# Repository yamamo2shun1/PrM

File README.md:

PrM
===

Modularized Analog mixer Controlled by Open Sound Control

License
---
<br /><span xmlns:dct="http://purl.org/dc/terms/" property="dct:title">PrM</span> is licensed under a <a rel="license" href="http://creativecommons.org/licenses/by-sa/4.0/">Creative Commons Attribution-ShareAlike 4.0 International License</a>.<br />Based on a work at <a xmlns:dct="http://purl.org/dc/terms/" href="https://github.com/tkrworks/PrM" rel="dct:source">https://github.com/tkrworks/PrM</a>.

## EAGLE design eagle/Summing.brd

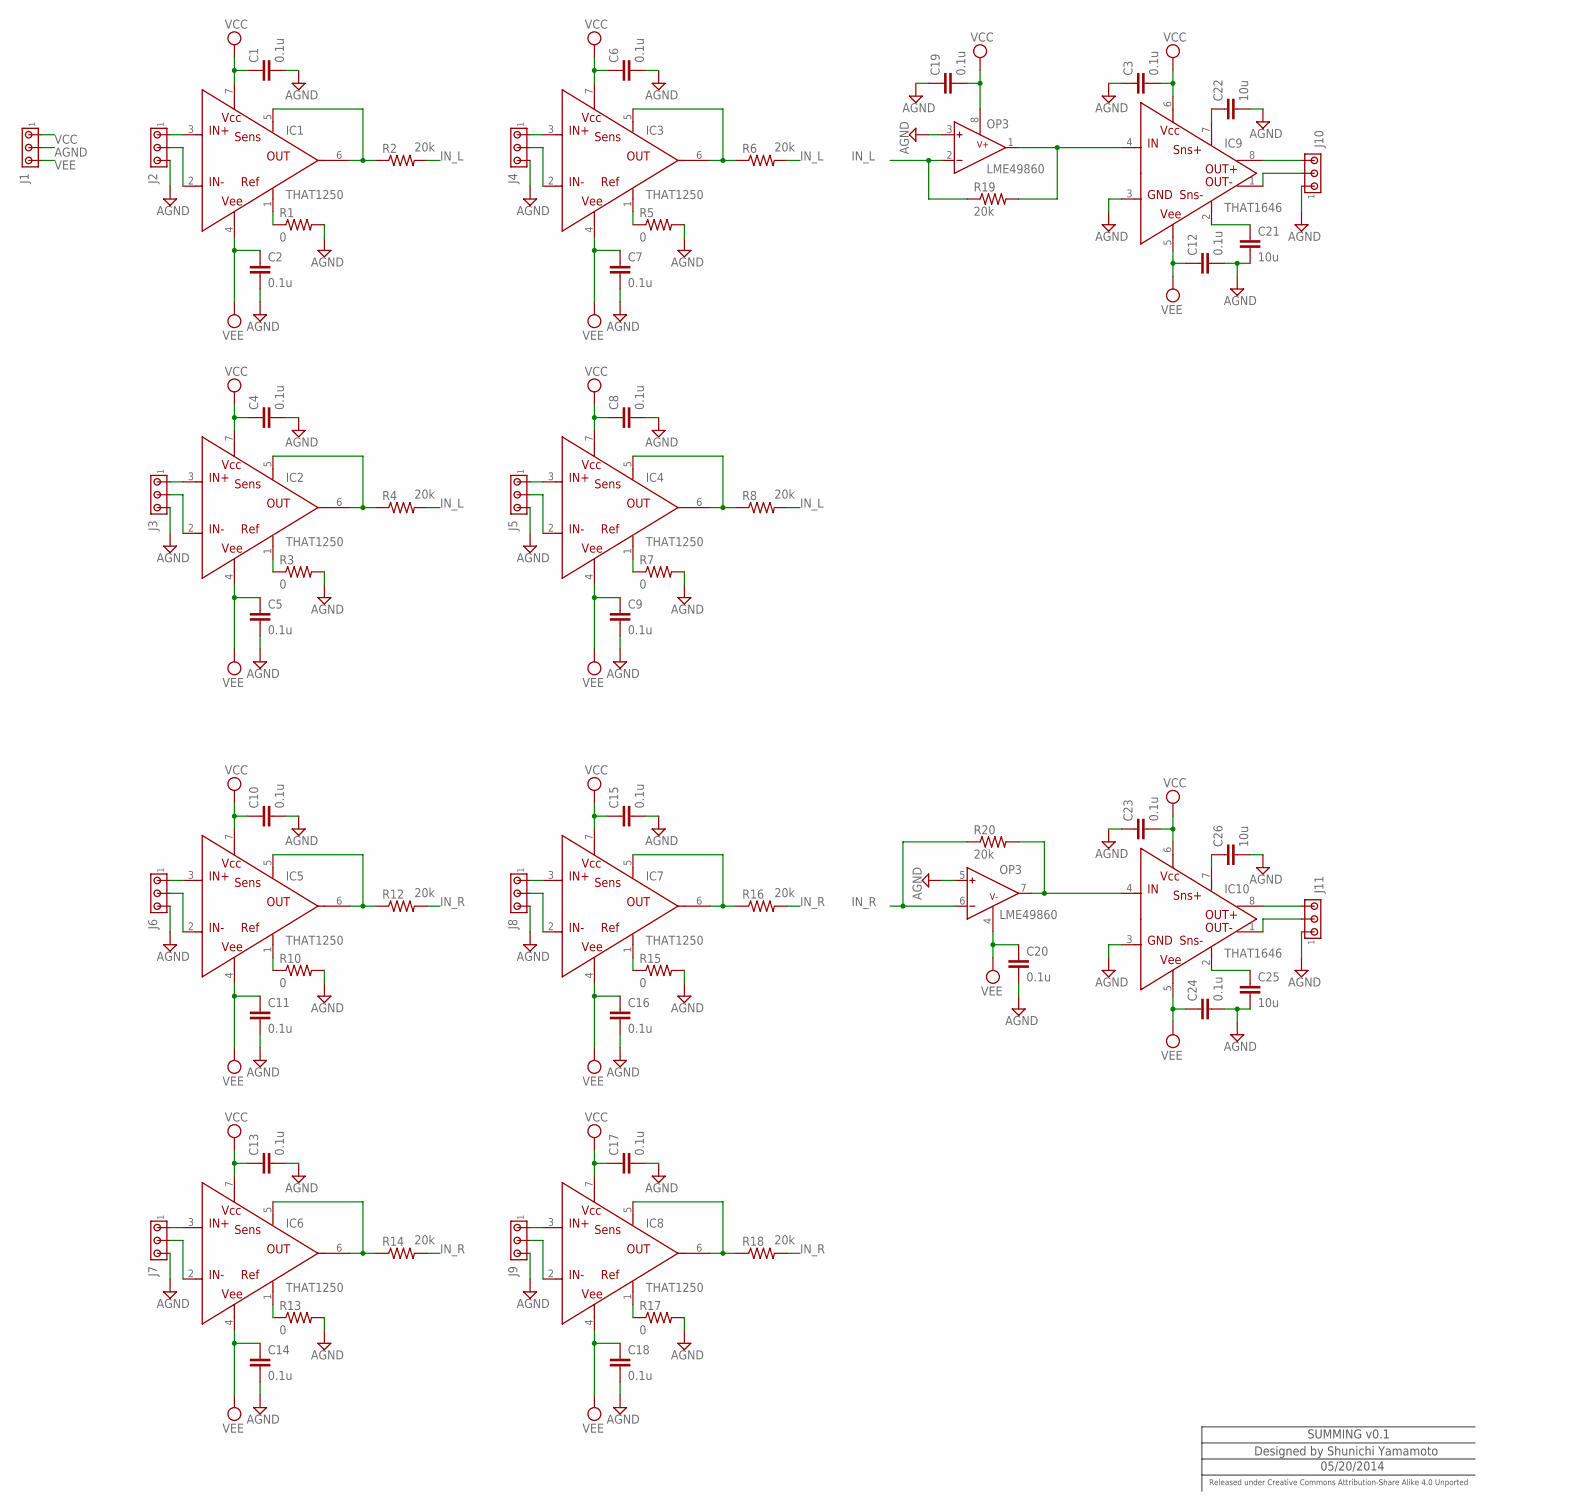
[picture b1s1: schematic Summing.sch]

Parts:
C1, C2, C3, C4, C5, C6, C7, C8, C9, C10, C11, C12, C13, C14, C15, C16, C17, C18, C19, C20, C23, C24: 0.1u; C2012
C21, C22, C25, C26: 10u; C2012
IC1, IC2, IC3, IC4, IC5, IC6, IC7, IC8: THAT1250; SOIC8@1
IC9, IC10: THAT1646; SOIC8
J1: MTA03-156; 1X3MTA
J2, J3, J4, J5, J6, J7, J8, J9, J10, J11: MTA03-100; 10X03MTA
OP3: LME49860; SOIC8@2
R1, R3, R5, R7, R10, R13, R15, R17: 0; 0805
R2, R4, R6, R8, R12, R14, R16, R18, R19, R20: 20k; 0805

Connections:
AGND: C1.2, C2.2, C3.1, C4.2, C5.2, C6.2, C7.2, C8.2, C9.2, C10.2, C11.2, C12.2, C13.2, C14.2, C15.2, C16.2, C17.2, C18.2, C19.1, C20.2, C21.2, C22.2, C23.1, C24.2, C25.2, C26.2, IC9.3 (GND), IC10.3 (GND), J1.2, J2.3, J3.3, J4.3, J5.3, J6.3, J7.3, J8.3, J9.3, J10.1, J11.1, OP3.3 (INA+), OP3.5 (INB+), R1.2, R3.2, R5.2, R7.2, R10.2, R13.2, R15.2, R17.2
IN_L: OP3.2 (INA-), R2.2, R4.2, R6.2, R8.2, R19.1
IN_R: OP3.6 (INB-), R12.2, R14.2, R16.2, R18.2, R20.1
MGAIN_L2: IC9.4 (IN), OP3.1 (OUTA), R19.2
MGAIN_R: IC10.4 (IN), OP3.7 (OUTB), R20.2
unnamed: IC1.1 (REF), R1.1
unnamed: IC2.1 (REF), R3.1
unnamed: IC1.3 (IN+), J2.1
unnamed: IC1.2 (IN-), J2.2
unnamed: IC2.3 (IN+), J3.1
unnamed: IC2.2 (IN-), J3.2
unnamed: IC3.1 (REF), R5.1
unnamed: IC3.3 (IN+), J4.1
unnamed: IC3.2 (IN-), J4.2
unnamed: IC4.1 (REF), R7.1
unnamed: IC4.3 (IN+), J5.1
unnamed: IC4.2 (IN-), J5.2
unnamed: IC5.1 (REF), R10.1
unnamed: IC5.3 (IN+), J6.1
unnamed: IC5.2 (IN-), J6.2
unnamed: IC6.1 (REF), R13.1
unnamed: IC6.3 (IN+), J7.1
unnamed: IC6.2 (IN-), J7.2
unnamed: IC7.1 (REF), R15.1
unnamed: IC7.3 (IN+), J8.1
unnamed: IC7.2 (IN-), J8.2
unnamed: IC8.1 (REF), R17.1
unnamed: IC8.3 (IN+), J9.1
unnamed: IC8.2 (IN-), J9.2
unnamed: C22.1, IC9.7 (SNS+)
unnamed: IC9.8 (OUT+), J10.3
unnamed: IC9.1 (OUT-), J10.2
unnamed: C26.1, IC10.7 (SNS+)
unnamed: C25.1, IC10.2 (SNS-)
unnamed: IC10.8 (OUT+), J11.3
unnamed: IC10.1 (OUT-), J11.2
unnamed: C21.1, IC9.2 (SNS-)
PIN_L: IC1.5 (SENS), IC1.6 (OUT), R2.1
PIN_L1: IC2.5 (SENS), IC2.6 (OUT), R4.1
PIN_L2: IC3.5 (SENS), IC3.6 (OUT), R6.1
PIN_L3: IC4.5 (SENS), IC4.6 (OUT), R8.1
PIN_L4: IC5.5 (SENS), IC5.6 (OUT), R12.1
PIN_L5: IC6.5 (SENS), IC6.6 (OUT), R14.1
PIN_L6: IC7.5 (SENS), IC7.6 (OUT), R16.1
PIN_L7: IC8.5 (SENS), IC8.6 (OUT), R18.1
VCC: C1.1, C3.2, C4.1, C6.1, C8.1, C10.1, C13.1, C15.1, C17.1, C19.2, C23.2, IC1.7 (VCC), IC2.7 (VCC), IC3.7 (VCC), IC4.7 (VCC), IC5.7 (VCC), IC6.7 (VCC), IC7.7 (VCC), IC8.7 (VCC), IC9.6 (VCC), IC10.6 (VCC), J1.1, OP3.8 (V+)
VEE: C2.1, C5.1, C7.1, C9.1, C11.1, C12.1, C14.1, C16.1, C18.1, C20.1, C24.1, IC1.4 (VEE), IC2.4 (VEE), IC3.4 (VEE), IC4.4 (VEE), IC5.4 (VEE), IC6.4 (VEE), IC7.4 (VEE), IC8.4 (VEE), IC9.5 (VEE), IC10.5 (VEE), J1.3, OP3.4 (V-)

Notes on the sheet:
SUMMING v0.1
Designed by Shunichi Yamamoto
05/20/2014
Released under Creative Commons Attribution-Share Alike 4.0 Unported

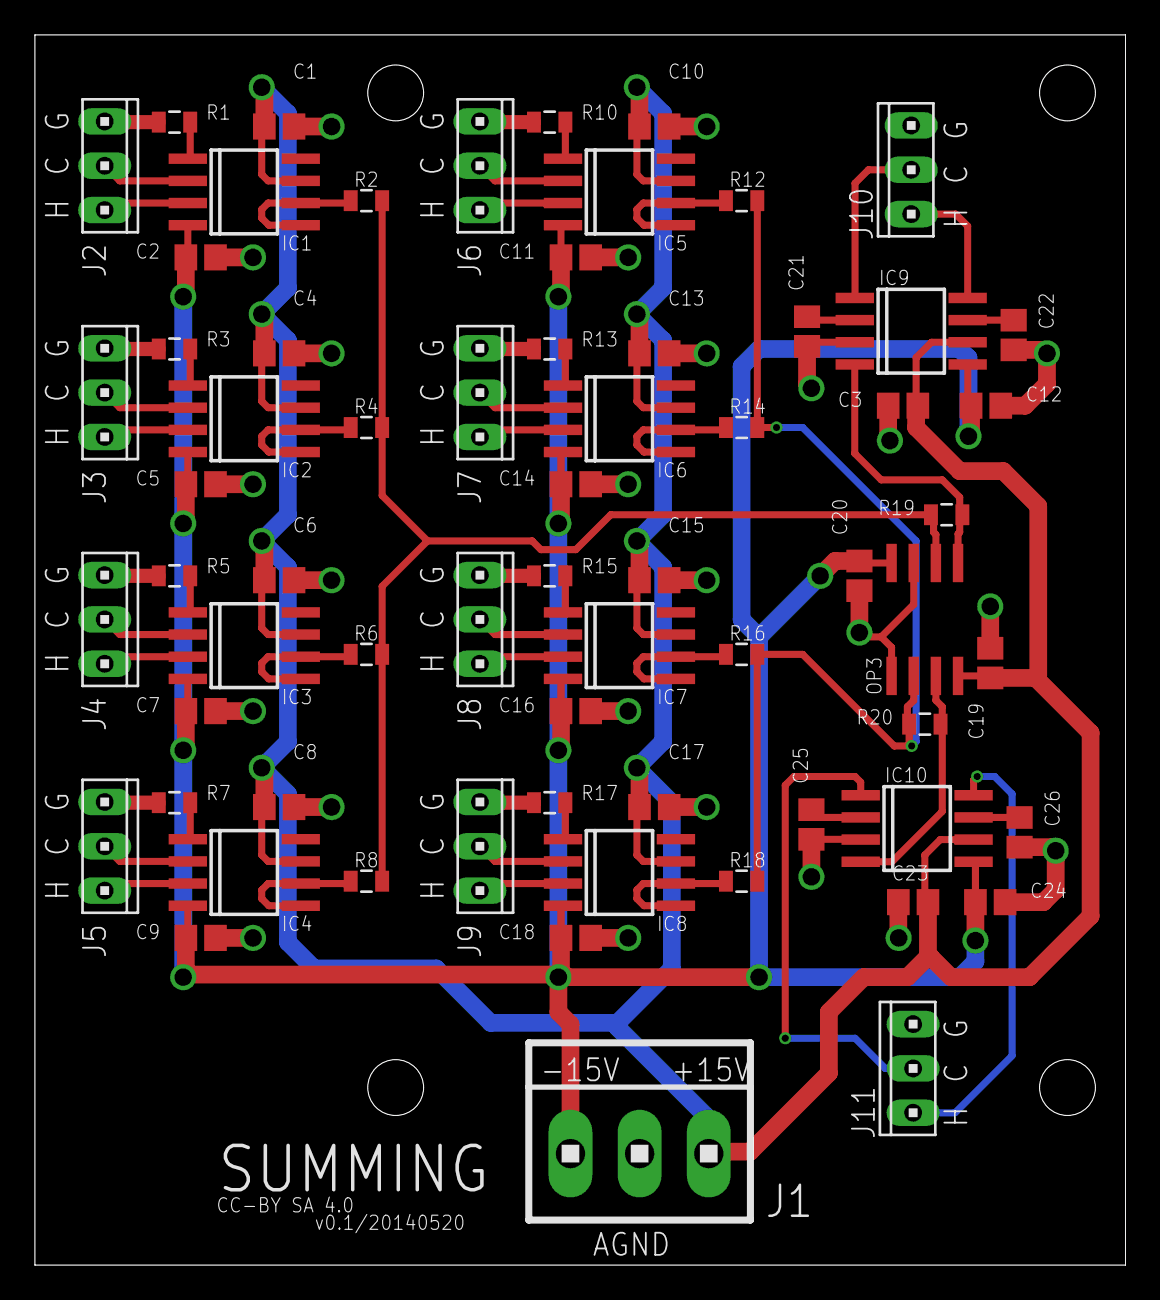
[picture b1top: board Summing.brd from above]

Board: 4 copper layers, 62.5 x 70.5 mm, 66 parts (0 on the bottom side), 47 nets.

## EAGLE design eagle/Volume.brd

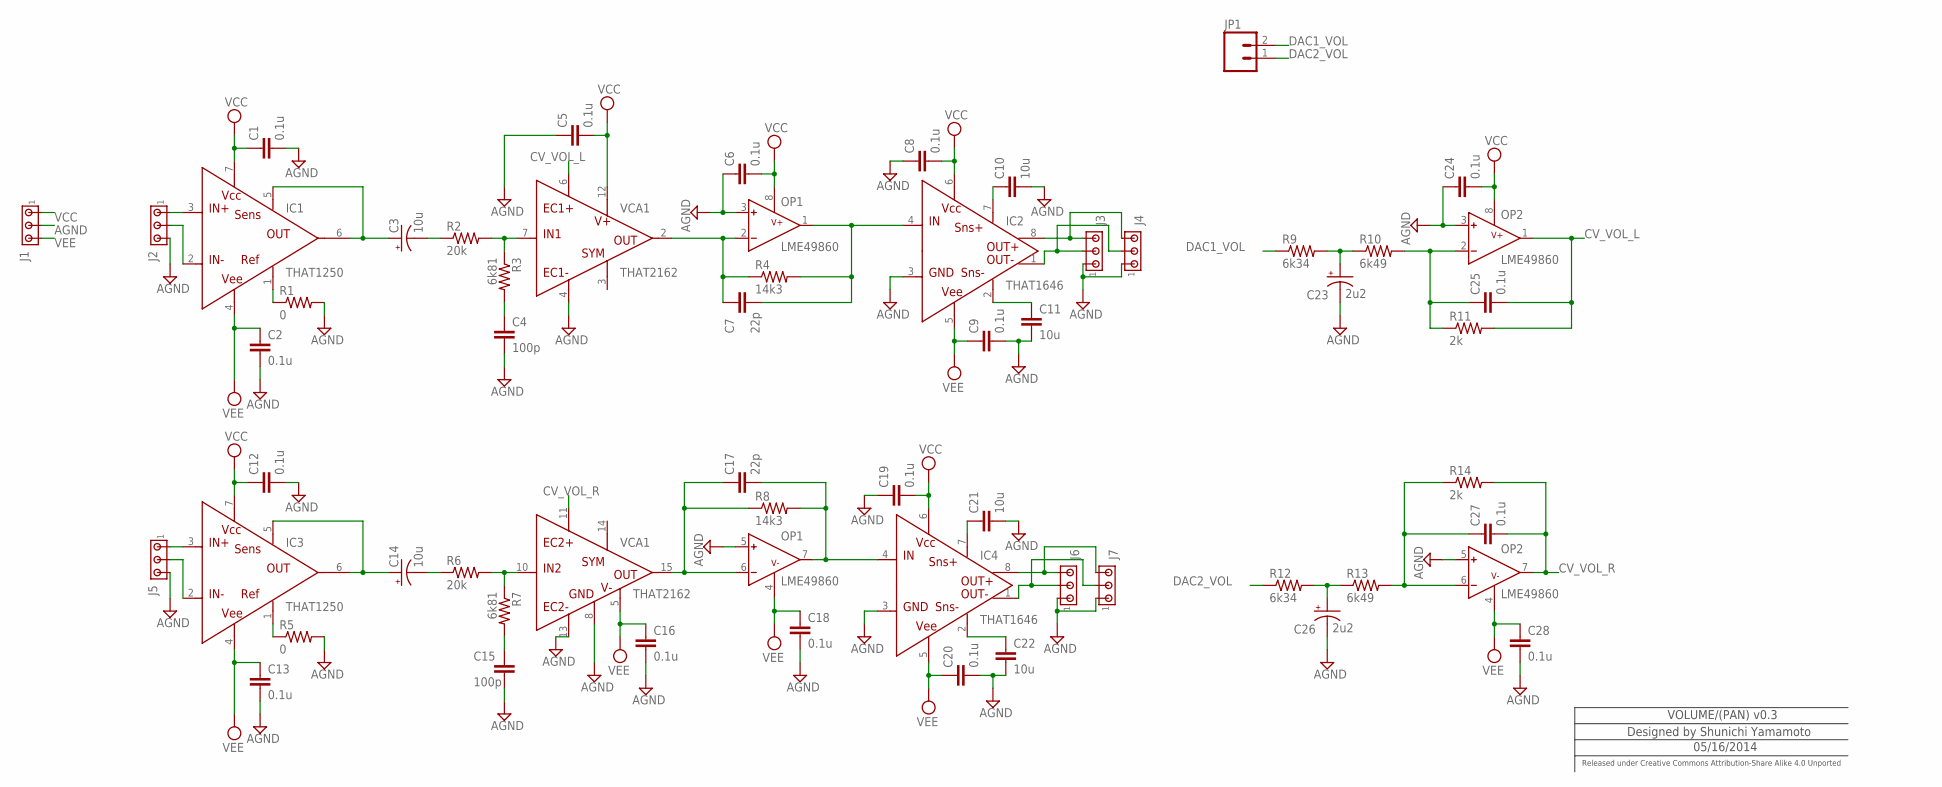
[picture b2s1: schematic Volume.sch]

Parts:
C1, C2, C5, C6, C8, C9, C12, C13, C16, C18, C19, C20, C24, C25, C27, C28: 0.1u; C2012
C3, C14: 10u; UD-5X5,8_NICHICON
C4, C15: 100p; C2012
C7, C17: 22p; C2012
C10, C11, C21, C22: 10u; C2012
C23, C26: 2u2; UD-5X5,8_NICHICON
IC1, IC3: THAT1250; SOIC8
IC2, IC4: THAT1646; SOIC8
J1: MTA03-156; 1X3MTA
J2, J3, J4, J5, J6, J7: MTA03-100; 10X03MTA
JP1: M02PTH; 1X02
OP1, OP2: LME49860; SOIC8@1
R1, R5: 0; 0805
R2, R6: 20k; 0805
R3, R7: 6k81; 0805
R4, R8: 14k3; 0805
R9, R12: 6k34; 0805
R10, R13: 6k49; 0805
R11, R14: 2k; 0805
VCA1: THAT2162; QSOP-16

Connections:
AGND: C1.2, C2.2, C4.2, C5.1, C6.1, C8.1, C9.2, C10.2, C11.2, C12.2, C13.2, C15.2, C16.2, C18.2, C19.1, C20.2, C21.2, C22.2, C23.-, C24.1, C26.-, C28.2, IC2.3 (GND), IC4.3 (GND), J1.2, J2.3, J3.1, J4.1, J5.3, J6.1, J7.1, OP1.3 (INA+), OP1.5 (INB+), OP2.3 (INA+), OP2.5 (INB+), R1.2, R5.2, VCA1.4 (EC1-), VCA1.8 (GND), VCA1.13 (EC2-)
C8: C14.-, R6.1
CV_VOL_L: C25.2, OP2.1 (OUTA), R11.2, VCA1.6 (EC1+)
CV_VOL_R: C27.2, OP2.7 (OUTB), R14.2, VCA1.11 (EC2+)
DAC1_VOL: JP1.2, R9.1
DAC2_VOL: JP1.1, R12.1
unnamed: IC1.1 (REF), R1.1
unnamed: C10.1, IC2.7 (SNS+)
unnamed: IC1.3 (IN+), J2.1
unnamed: IC1.2 (IN-), J2.2
unnamed: IC3.1 (REF), R5.1
unnamed: IC3.3 (IN+), J5.1
unnamed: IC3.2 (IN-), J5.2
unnamed: IC2.8 (OUT+), J3.3, J4.3
unnamed: IC2.1 (OUT-), J3.2, J4.2
unnamed: IC4.8 (OUT+), J6.3, J7.3
unnamed: IC4.1 (OUT-), J6.2, J7.2
unnamed: R2.2, R3.1, VCA1.7 (IN1)
unnamed: C11.1, IC2.2 (SNS-)
unnamed: C21.1, IC4.7 (SNS+)
unnamed: C22.1, IC4.2 (SNS-)
unnamed: C3.-, R2.1
unnamed: R6.2, R7.1, VCA1.10 (IN2)
unnamed: C7.1, OP1.2 (INA-), R4.1, VCA1.2 (OUT1)
unnamed: C4.1, R3.2
unnamed: C15.1, R7.2
unnamed: C23.+, R9.2, R10.1
unnamed: C25.1, OP2.2 (INA-), R10.2, R11.1
unnamed: C26.+, R12.2, R13.1
unnamed: C27.1, OP2.6 (INB-), R13.2, R14.1
unnamed: C17.1, OP1.6 (INB-), R8.1, VCA1.15 (OUT2)
OUT_L: C7.2, IC2.4 (IN), OP1.1 (OUTA), R4.2
OUT_R: C17.2, IC4.4 (IN), OP1.7 (OUTB), R8.2
PIN_L: C3.+, IC1.5 (SENS), IC1.6 (OUT)
PIN_R: C14.+, IC3.5 (SENS), IC3.6 (OUT)
VCC: C1.1, C5.2, C6.2, C8.2, C12.1, C19.2, C24.2, IC1.7 (VCC), IC2.6 (VCC), IC3.7 (VCC), IC4.6 (VCC), J1.1, OP1.8 (V+), OP2.8 (V+), VCA1.12 (V+)
VEE: C2.1, C9.1, C13.1, C16.1, C18.1, C20.1, C28.1, IC1.4 (VEE), IC2.5 (VEE), IC3.4 (VEE), IC4.5 (VEE), J1.3, OP1.4 (V-), OP2.4 (V-), VCA1.5 (V-)

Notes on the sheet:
VOLUME/(PAN) v0.3
Designed by Shunichi Yamamoto
05/16/2014
Released under Creative Commons Attribution-Share Alike 4.0 Unported

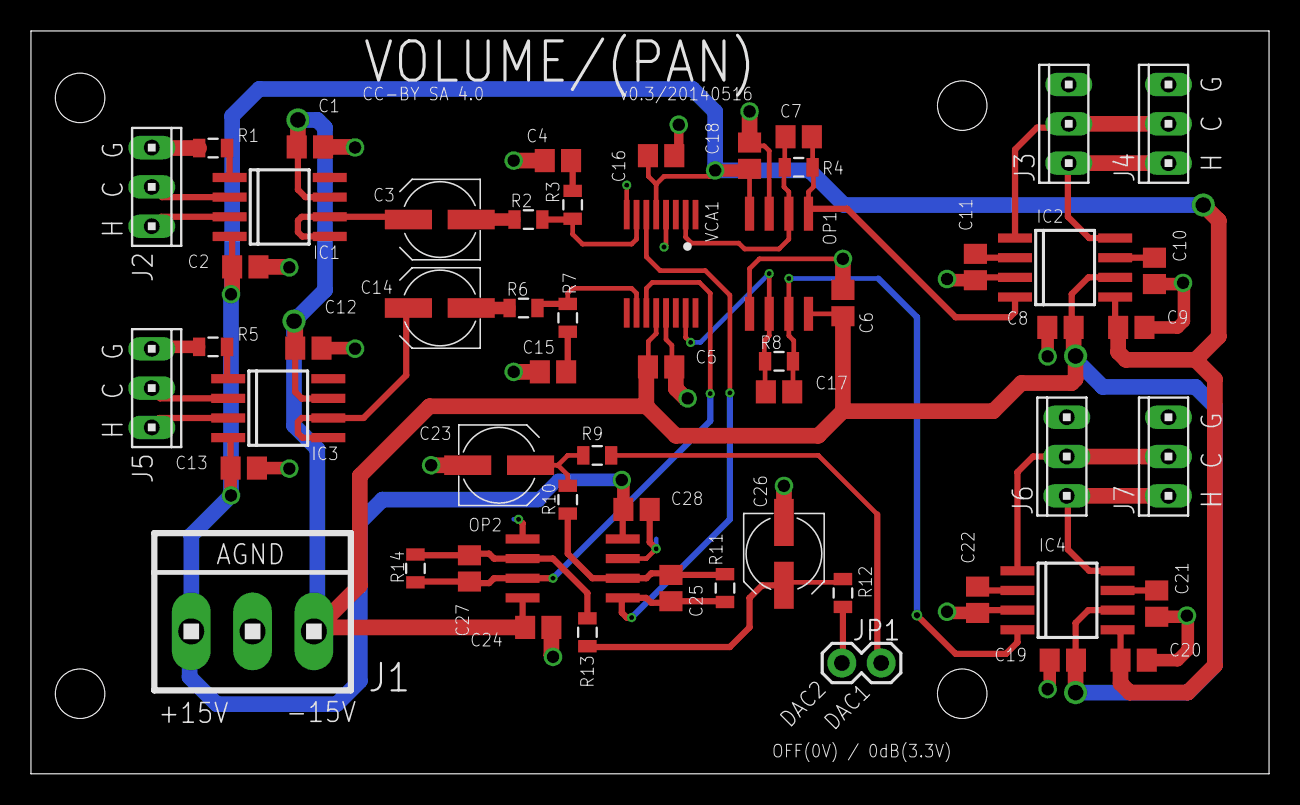
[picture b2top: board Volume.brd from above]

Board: 2 copper layers, 80.0 x 48.0 mm, 57 parts (0 on the bottom side), 37 nets.

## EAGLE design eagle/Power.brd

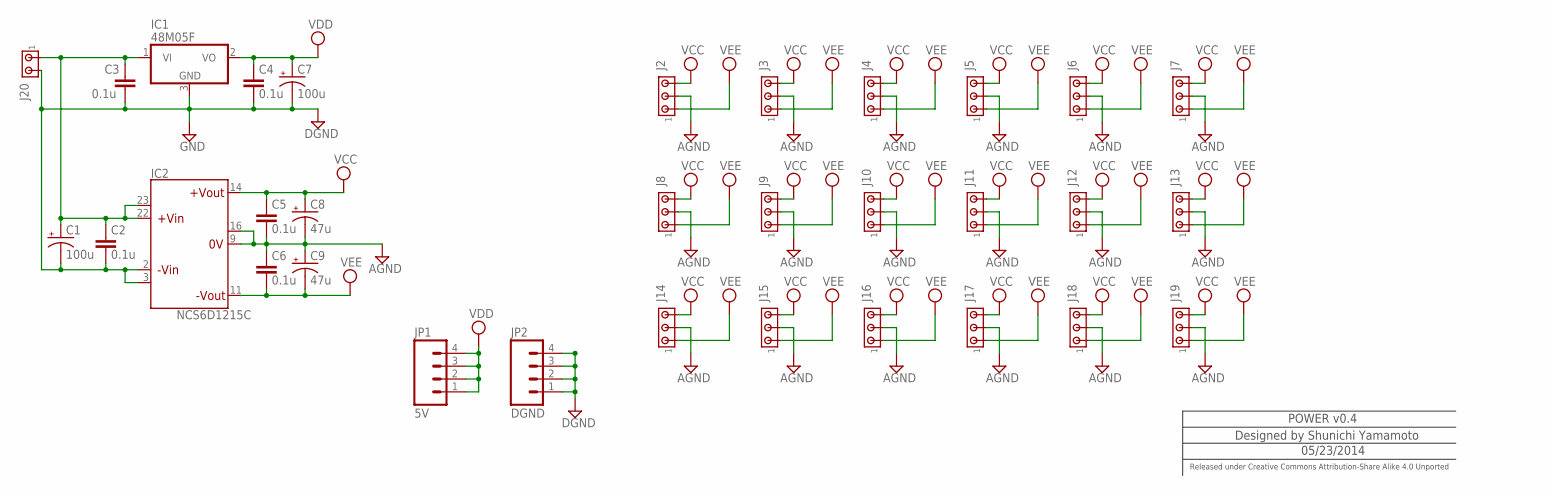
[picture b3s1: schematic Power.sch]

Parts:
C1, C7: 100u; UD-6,3X7,7_NICHICON
C2, C3, C4, C5, C6: 0.1u; C2012
C8, C9: 47u; UD-5X5,8_NICHICON
IC1: 48M05F; TO252
IC2: NCS6D1215C
J2, J3, J4, J5, J6, J7, J8, J9, J10, J11, J12, J13, J14, J15, J16, J17, J18, J19: MTA03-156; 1X3MTA
J20: MTA02-156; 1X2MTA
JP1: 5V; 1X04
JP2: DGND; 1X04

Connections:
AGND: C5.2, C6.1, C8.-, C9.+, IC2.9 (0V), IC2.16 (0V2), J2.2, J3.2, J4.2, J5.2, J6.2, J7.2, J8.2, J9.2, J10.2, J11.2, J12.2, J13.2, J14.2, J15.2, J16.2, J17.2, J18.2, J19.2
GND: C1.-, C2.2, C3.2, C4.2, C7.-, IC1.3 (GND), IC2.2 (-VIN), IC2.3 (-VIN2), J20.2, JP2.1, JP2.2, JP2.3, JP2.4
unnamed: C1.+, C2.1, C3.1, IC1.1 (VI), IC2.22 (+VIN), IC2.23 (+VIN2), J20.1
VCC: C5.1, C8.+, IC2.14 (+VOUT), J2.3, J3.3, J4.3, J5.3, J6.3, J7.3, J8.3, J9.3, J10.3, J11.3, J12.3, J13.3, J14.3, J15.3, J16.3, J17.3, J18.3, J19.3
VDD: C4.1, C7.+, IC1.2 (VO), JP1.1, JP1.2, JP1.3, JP1.4
VEE: C6.2, C9.-, IC2.11 (-VOUT), J2.1, J3.1, J4.1, J5.1, J6.1, J7.1, J8.1, J9.1, J10.1, J11.1, J12.1, J13.1, J14.1, J15.1, J16.1, J17.1, J18.1, J19.1

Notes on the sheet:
POWER v0.4
Designed by Shunichi Yamamoto
05/23/2014
Released under Creative Commons Attribution-Share Alike 4.0 Unported

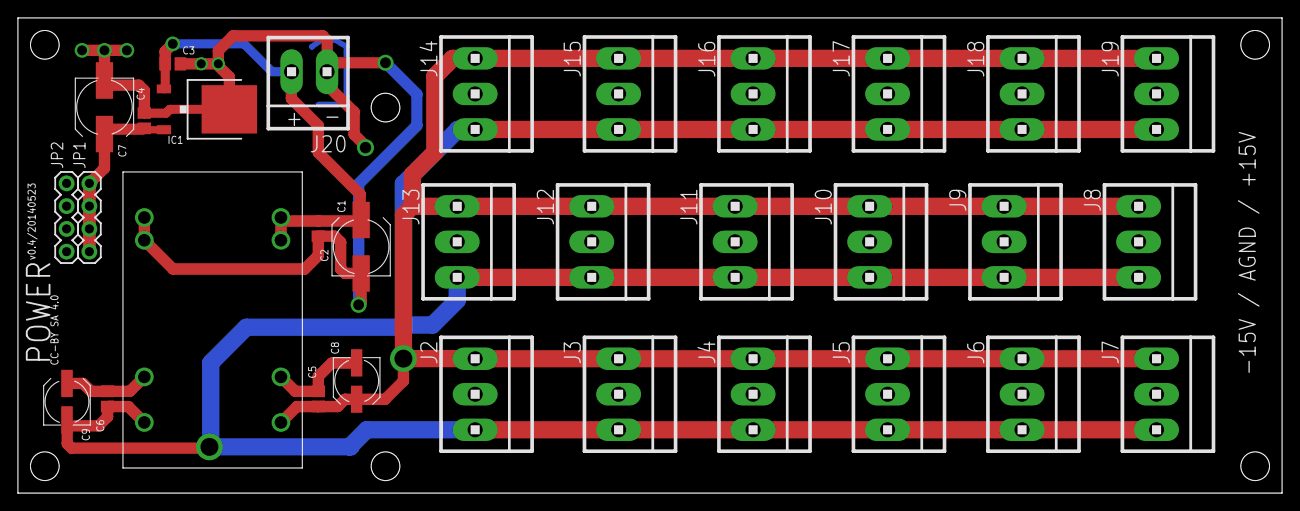
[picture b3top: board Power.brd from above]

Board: 2 copper layers, 141.0 x 53.0 mm, 32 parts (0 on the bottom side), 6 nets.

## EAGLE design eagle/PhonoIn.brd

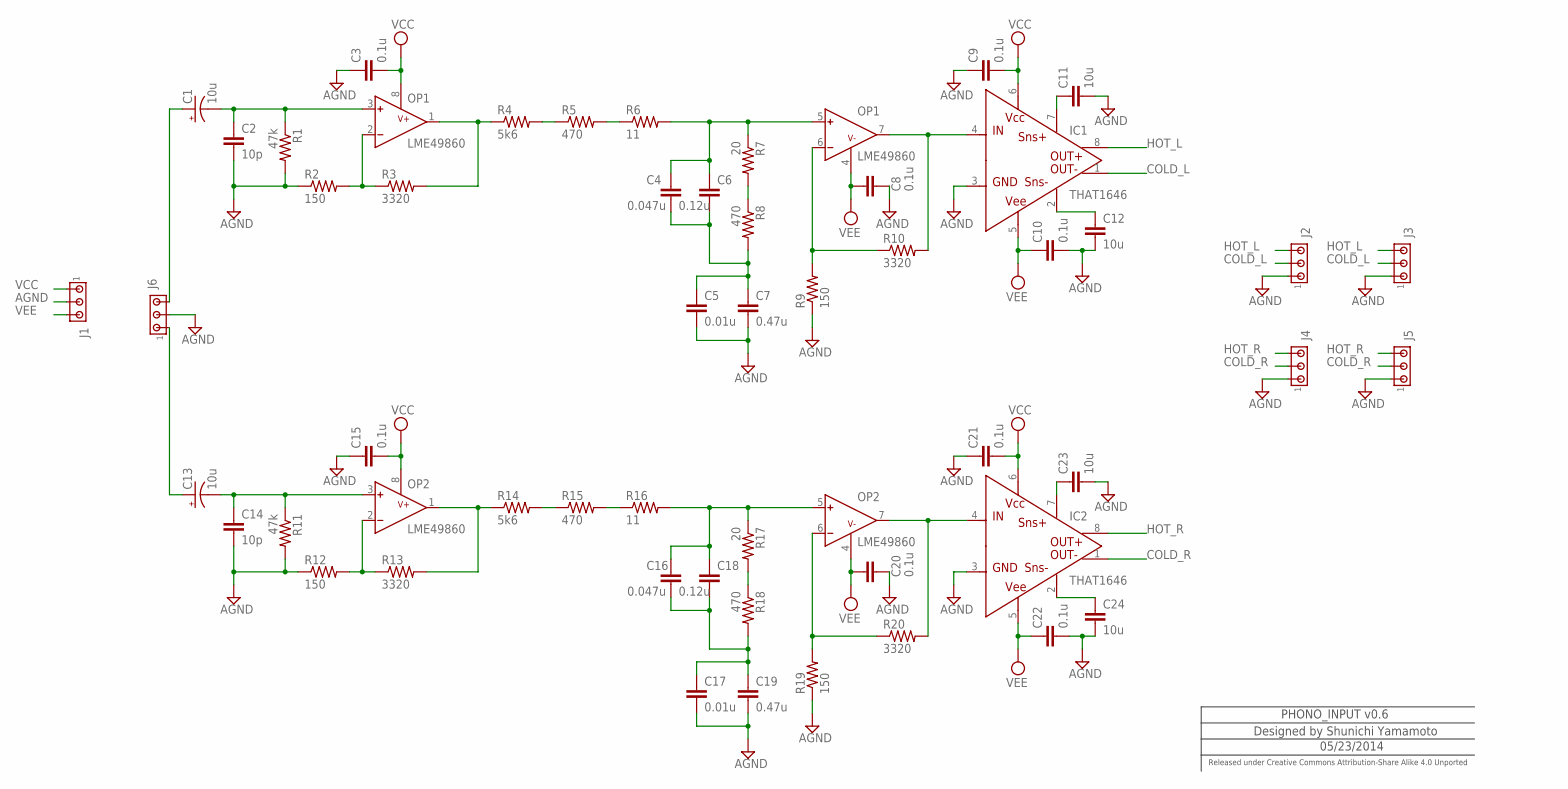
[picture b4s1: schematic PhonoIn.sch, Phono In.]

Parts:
C1, C13: 10u; UD-5X5,8_NICHICON
C2, C14: 10p; C1608
C3, C8, C9, C10, C15, C20, C21, C22: 0.1u; C2012
C4, C16: 0.047u; C4833
C5, C17: 0.01u; C3216
C6, C18: 0.12u; C6041
C7, C19: 0.47u; C5750
C11, C12, C23, C24: 10u; C2012
IC1, IC2: THAT1646; SOIC8
J1: MTA03-156; 1X3MTA
J2, J3, J4, J5, J6: MTA03-100; 10X03MTA
OP1, OP2: LME49860; SOIC8
R1, R11: 47k; 0805
R2, R9, R12, R19: 150; 0805
R3, R10, R13, R20: 3320; 0805
R4, R14: 5k6; 0805
R5, R8, R15, R18: 470; 0805
R6, R16: 11; 0805
R7, R17: 20; 0805

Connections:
AGND: C2.2, C3.1, C5.2, C7.P$2 (2), C8.2, C9.1, C10.2, C11.2, C12.2, C14.2, C15.1, C17.2, C19.P$2 (2), C20.2, C21.1, C22.2, C23.2, C24.2, IC1.3 (GND), IC2.3 (GND), J1.2, J2.1, J3.1, J4.1, J5.1, J6.2, R1.2, R2.1, R9.1, R11.2, R12.1, R19.1
COLD_L: IC1.1 (OUT-), J2.2, J3.2
COLD_R: IC2.1 (OUT-), J4.2, J5.2
HOT_L: IC1.8 (OUT+), J2.3, J3.3
HOT_R: IC2.8 (OUT+), J4.3, J5.3
unnamed: R5.2, R6.1
unnamed: R15.2, R16.1
unnamed: C11.1, IC1.7 (SNS+)
unnamed: C1.-, C2.1, OP1.3 (INA+), R1.1
unnamed: C13.-, C14.1, OP2.3 (INA+), R11.1
unnamed: C23.1, IC2.7 (SNS+)
unnamed: C12.1, IC1.2 (SNS-)
unnamed: C24.1, IC2.2 (SNS-)
unnamed: OP1.2 (INA-), R2.2, R3.1
unnamed: OP1.1 (OUTA), R3.2, R4.1
unnamed: C4.2, C5.1, C6.2, C7.P$1 (1), R8.2
unnamed: C1.+, J6.3
unnamed: R4.2, R5.1
unnamed: C4.1, C6.1, OP1.5 (INB+), R6.2, R7.1
unnamed: R7.2, R8.1
unnamed: OP1.6 (INB-), R9.2, R10.1
unnamed: C13.+, J6.1
unnamed: OP2.2 (INA-), R12.2, R13.1
unnamed: OP2.1 (OUTA), R13.2, R14.1
unnamed: R14.2, R15.1
unnamed: C16.1, C18.1, OP2.5 (INB+), R16.2, R17.1
unnamed: R17.2, R18.1
unnamed: C16.2, C17.1, C18.2, C19.P$1 (1), R18.2
unnamed: OP2.6 (INB-), R19.2, R20.1
PIN_L: IC1.4 (IN), OP1.7 (OUTB), R10.2
PIN_R: IC2.4 (IN), OP2.7 (OUTB), R20.2
VCC: C3.2, C9.2, C15.2, C21.2, IC1.6 (VCC), IC2.6 (VCC), J1.1, OP1.8 (V+), OP2.8 (V+)
VEE: C8.1, C10.1, C20.1, C22.1, IC1.5 (VEE), IC2.5 (VEE), J1.3, OP1.4 (V-), OP2.4 (V-)

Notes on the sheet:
PHONO_INPUT v0.6
Designed by Shunichi Yamamoto
05/23/2014
Released under Creative Commons Attribution-Share Alike 4.0 Unported

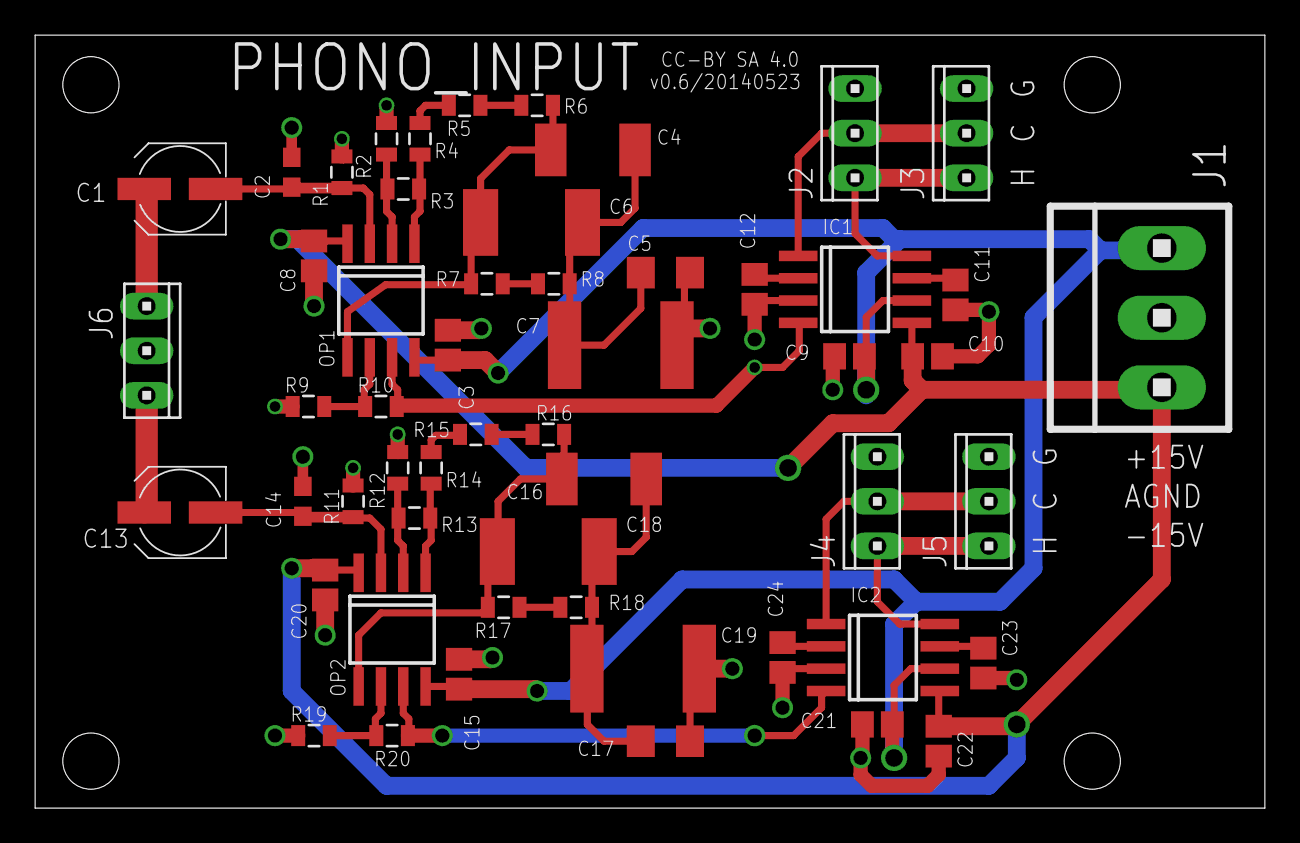
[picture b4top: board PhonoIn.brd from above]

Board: 2 copper layers, 70.0 x 44.0 mm, 54 parts (0 on the bottom side), 33 nets.

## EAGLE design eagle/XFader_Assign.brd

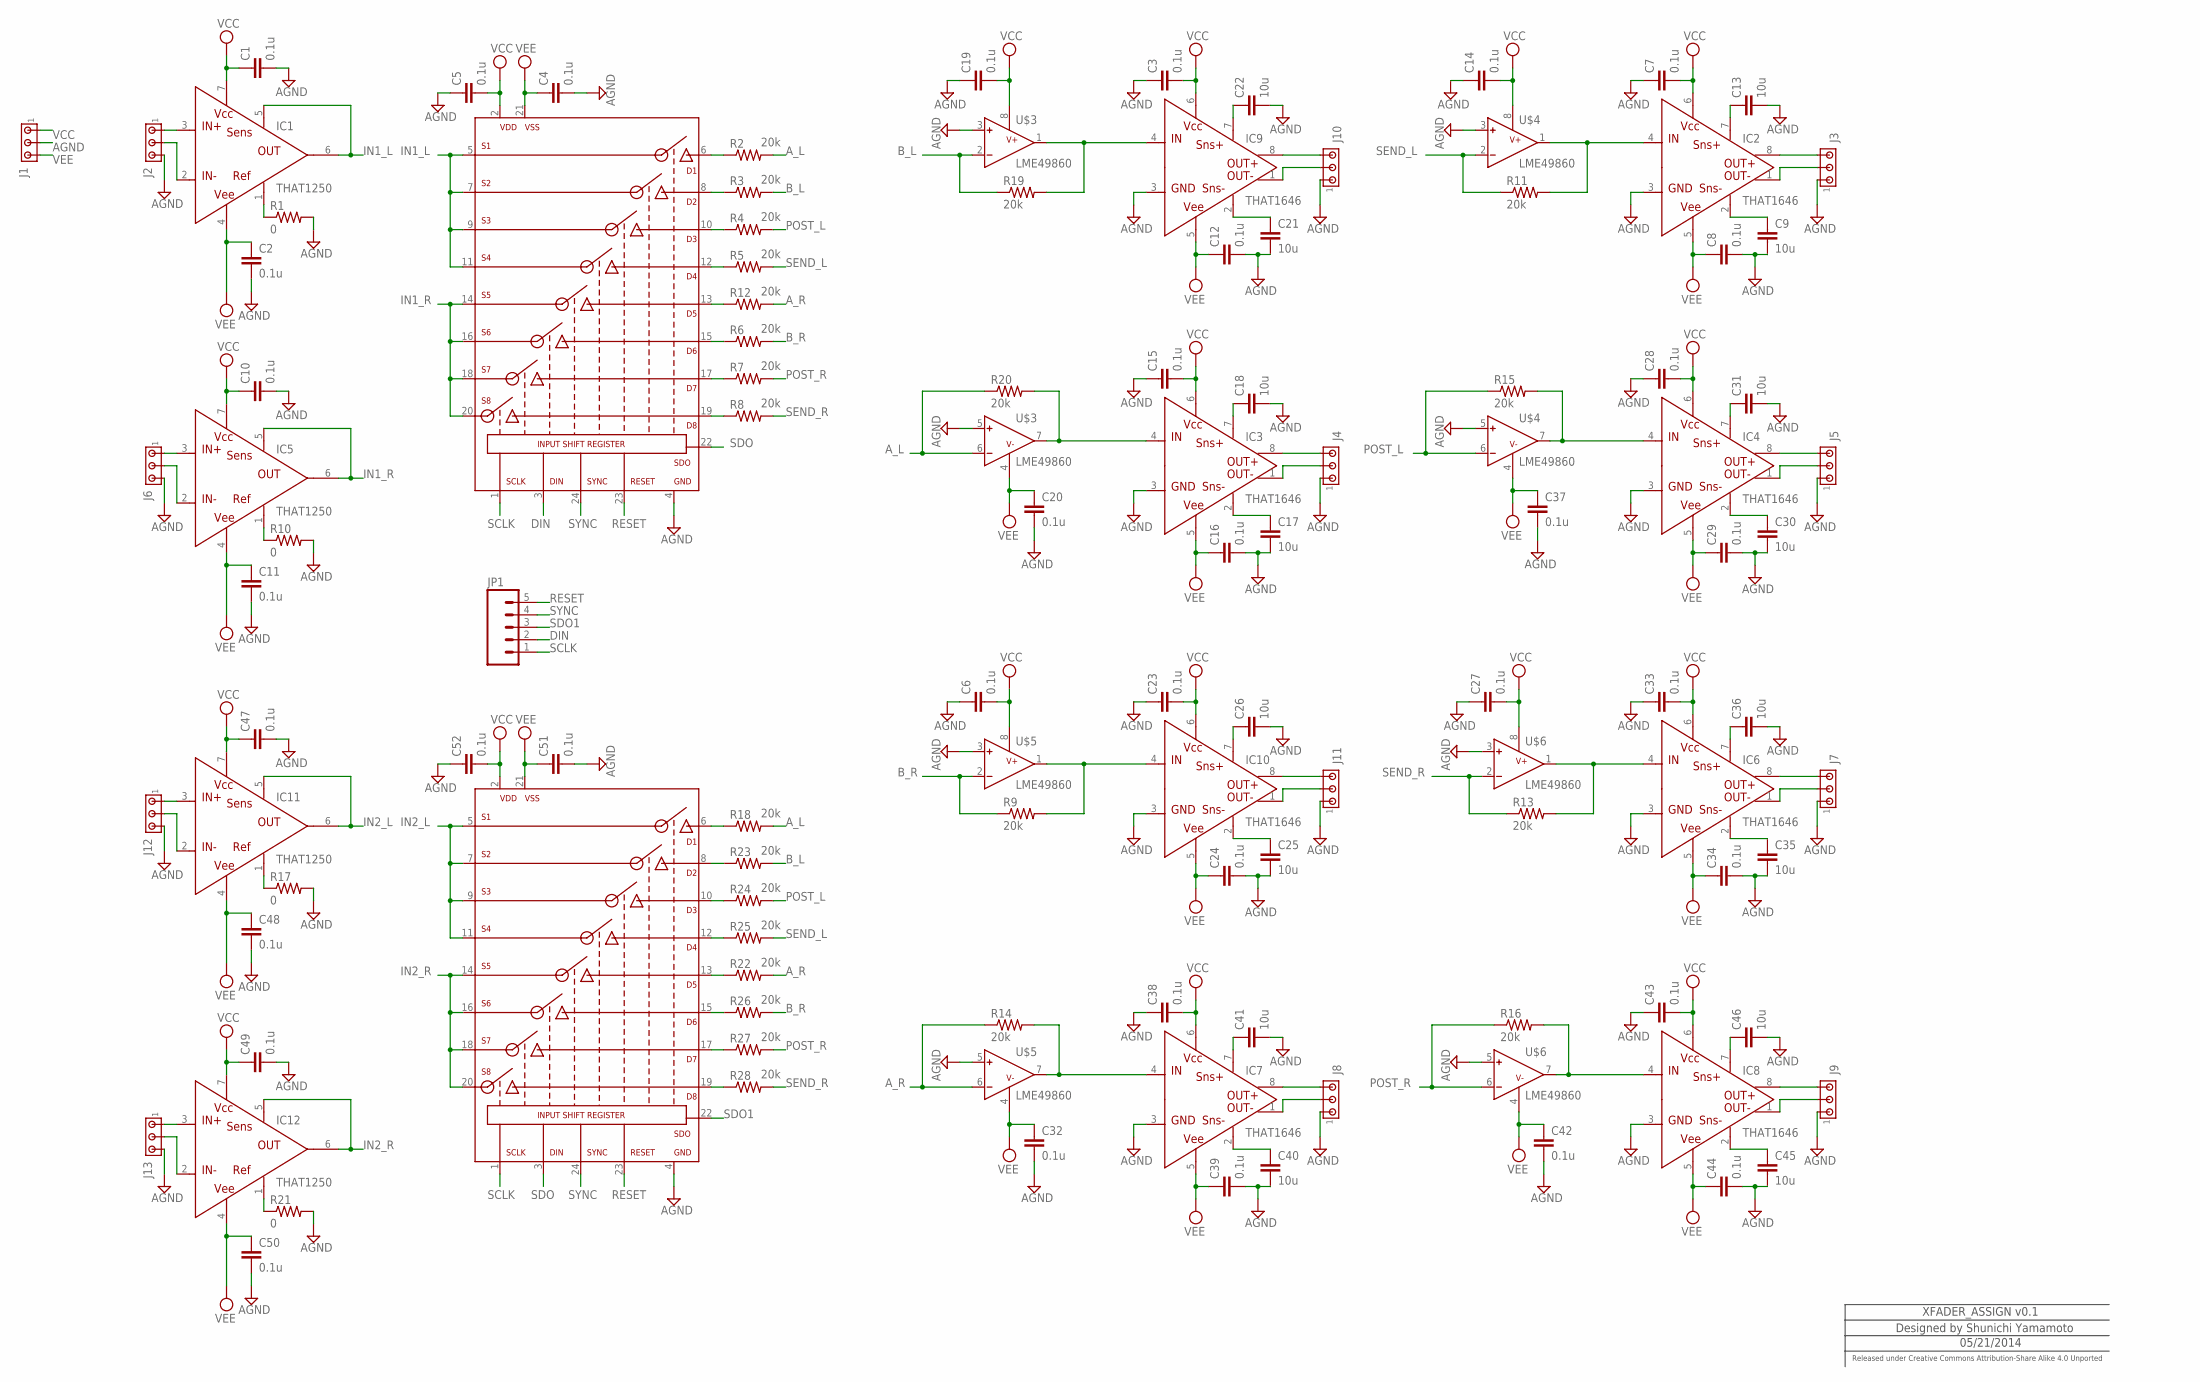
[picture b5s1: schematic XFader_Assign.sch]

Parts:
C1, C2, C3, C4, C5, C6, C7, C8, C10, C11, C12, C14, C15, C16, C19, C20, C23, C24, C27, C28, C29, C32, C33, C34, C37, C38, C39, C42, C43, C44, C47, C48, C49, C50, C51, C52: 0.1u; C2012
C9, C13, C17, C18, C21, C22, C25, C26, C30, C31, C35, C36, C40, C41, C45, C46: 10u; C2012
IC1, IC5, IC11, IC12: THAT1250; SOIC8@1
IC2, IC3, IC4, IC6, IC7, IC8, IC9, IC10: THAT1646; SOIC8
J1: MTA03-156; 1X3MTA
J2, J3, J4, J5, J6, J7, J8, J9, J10, J11, J12, J13: MTA03-100; 10X03MTA
JP1: M05PTH; 1X05
R1, R10, R17, R21: 0; 0805
R2, R3, R4, R5, R6, R7, R8, R9, R11, R12, R13, R14, R15, R16, R18, R19, R20, R22, R23, R24, R25, R26, R27, R28: 20k; 0805
U$1, U$2: ADG1414; TSSOP24
U$3, U$4, U$5, U$6: LME49860; SOIC8

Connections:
AGND: C1.2, C2.2, C3.1, C4.2, C5.1, C6.1, C7.1, C8.2, C9.2, C10.2, C11.2, C12.2, C13.2, C14.1, C15.1, C16.2, C17.2, C18.2, C19.1, C20.2, C21.2, C22.2, C23.1, C24.2, C25.2, C26.2, C27.1, C28.1, C29.2, C30.2, C31.2, C32.2, C33.1, C34.2, C35.2, C36.2, C37.2, C38.1, C39.2, C40.2, C41.2, C42.2, C43.1, C44.2, C45.2, C46.2, C47.2, C48.2, C49.2, C50.2, C51.2, C52.1, IC2.3 (GND), IC3.3 (GND), IC4.3 (GND), IC6.3 (GND), IC7.3 (GND), IC8.3 (GND), IC9.3 (GND), IC10.3 (GND), J1.2, J2.3, J3.1, J4.1, J5.1, J6.3, J7.1, J8.1, J9.1, J10.1, J11.1, J12.3, J13.3, R1.2, R10.2, R17.2, R21.2, U$1.4 (GND), U$2.4 (GND), U$3.3 (INA+), U$3.5 (INB+), U$4.3 (INA+), U$4.5 (INB+), U$5.3 (INA+), U$5.5 (INB+), U$6.3 (INA+), U$6.5 (INB+)
A_L: R2.2, R18.2, R20.1, U$3.6 (INB-)
A_R: R12.2, R14.1, R22.2, U$5.6 (INB-)
B_L: R3.2, R19.1, R23.2, U$3.2 (INA-)
B_R: R6.2, R9.1, R26.2, U$5.2 (INA-)
DIN: JP1.2, U$1.3 (DIN)
IN1_L: IC1.5 (SENS), IC1.6 (OUT), U$1.5 (S1), U$1.7 (S2), U$1.9 (S3), U$1.11 (S4)
IN1_R: IC5.5 (SENS), IC5.6 (OUT), U$1.14 (S5), U$1.16 (S6), U$1.18 (S7), U$1.20 (S8)
IN2_L: IC11.5 (SENS), IC11.6 (OUT), U$2.5 (S1), U$2.7 (S2), U$2.9 (S3), U$2.11 (S4)
IN2_R: IC12.5 (SENS), IC12.6 (OUT), U$2.14 (S5), U$2.16 (S6), U$2.18 (S7), U$2.20 (S8)
MGAIN_L1: IC10.4 (IN), R9.2, U$5.1 (OUTA)
MGAIN_L2: IC9.4 (IN), R19.2, U$3.1 (OUTA)
MGAIN_L3: IC2.4 (IN), R11.2, U$4.1 (OUTA)
MGAIN_L4: IC6.4 (IN), R13.2, U$6.1 (OUTA)
MGAIN_R: IC3.4 (IN), R20.2, U$3.7 (OUTB)
MGAIN_R1: IC7.4 (IN), R14.2, U$5.7 (OUTB)
MGAIN_R2: IC4.4 (IN), R15.2, U$4.7 (OUTB)
MGAIN_R3: IC8.4 (IN), R16.2, U$6.7 (OUTB)
unnamed: IC1.1 (REF), R1.1
unnamed: R2.1, U$1.6 (D1)
unnamed: IC1.3 (IN+), J2.1
unnamed: IC1.2 (IN-), J2.2
unnamed: R12.1, U$1.13 (D5)
unnamed: R3.1, U$1.8 (D2)
unnamed: R4.1, U$1.10 (D3)
unnamed: R5.1, U$1.12 (D4)
unnamed: R6.1, U$1.15 (D6)
unnamed: R7.1, U$1.17 (D7)
unnamed: R8.1, U$1.19 (D8)
unnamed: C13.1, IC2.7 (SNS+)
unnamed: IC5.1 (REF), R10.1
unnamed: IC5.3 (IN+), J6.1
unnamed: IC5.2 (IN-), J6.2
unnamed: C9.1, IC2.2 (SNS-)
unnamed: IC2.8 (OUT+), J3.3
unnamed: IC2.1 (OUT-), J3.2
unnamed: C18.1, IC3.7 (SNS+)
unnamed: C17.1, IC3.2 (SNS-)
unnamed: IC3.8 (OUT+), J4.3
unnamed: IC3.1 (OUT-), J4.2
unnamed: C31.1, IC4.7 (SNS+)
unnamed: C30.1, IC4.2 (SNS-)
unnamed: C22.1, IC9.7 (SNS+)
unnamed: IC9.8 (OUT+), J10.3
unnamed: IC9.1 (OUT-), J10.2
unnamed: C26.1, IC10.7 (SNS+)
unnamed: C25.1, IC10.2 (SNS-)
unnamed: IC10.8 (OUT+), J11.3
unnamed: IC10.1 (OUT-), J11.2
unnamed: IC4.8 (OUT+), J5.3
unnamed: IC4.1 (OUT-), J5.2
unnamed: C21.1, IC9.2 (SNS-)
unnamed: C36.1, IC6.7 (SNS+)
unnamed: C35.1, IC6.2 (SNS-)
unnamed: IC6.8 (OUT+), J7.3
unnamed: IC6.1 (OUT-), J7.2
unnamed: C41.1, IC7.7 (SNS+)
unnamed: C40.1, IC7.2 (SNS-)
unnamed: IC7.8 (OUT+), J8.3
unnamed: IC7.1 (OUT-), J8.2
unnamed: C46.1, IC8.7 (SNS+)
unnamed: C45.1, IC8.2 (SNS-)
unnamed: IC8.8 (OUT+), J9.3
unnamed: IC8.1 (OUT-), J9.2
unnamed: IC11.1 (REF), R17.1
unnamed: IC11.3 (IN+), J12.1
unnamed: IC11.2 (IN-), J12.2
unnamed: IC12.1 (REF), R21.1
unnamed: IC12.3 (IN+), J13.1
unnamed: IC12.2 (IN-), J13.2
unnamed: R18.1, U$2.6 (D1)
unnamed: R22.1, U$2.13 (D5)
unnamed: R23.1, U$2.8 (D2)
unnamed: R24.1, U$2.10 (D3)
unnamed: R25.1, U$2.12 (D4)
unnamed: R26.1, U$2.15 (D6)
unnamed: R27.1, U$2.17 (D7)
unnamed: R28.1, U$2.19 (D8)
POST_L: R4.2, R15.1, R24.2, U$4.6 (INB-)
POST_R: R7.2, R16.1, R27.2, U$6.6 (INB-)
RESET: JP1.5, U$1.23 (RESET), U$2.23 (RESET)
SCLK: JP1.1, U$1.1 (SCLK), U$2.1 (SCLK)
SDO: U$1.22 (SDO), U$2.3 (DIN)
SDO1: JP1.3, U$2.22 (SDO)
SEND_L: R5.2, R11.1, R25.2, U$4.2 (INA-)
SEND_R: R8.2, R13.1, R28.2, U$6.2 (INA-)
SYNC: JP1.4, U$1.24 (SYNC), U$2.24 (SYNC)
VCC: C1.1, C3.2, C5.2, C6.2, C7.2, C10.1, C14.2, C15.2, C19.2, C23.2, C27.2, C28.2, C33.2, C38.2, C43.2, C47.1, C49.1, C52.2, IC1.7 (VCC), IC2.6 (VCC), IC3.6 (VCC), IC4.6 (VCC), IC5.7 (VCC), IC6.6 (VCC), IC7.6 (VCC), IC8.6 (VCC), IC9.6 (VCC), IC10.6 (VCC), IC11.7 (VCC), IC12.7 (VCC), J1.1, U$1.2 (VDD), U$2.2 (VDD), U$3.8 (V+), U$4.8 (V+), U$5.8 (V+), U$6.8 (V+)
VEE: C2.1, C4.1, C8.1, C11.1, C12.1, C16.1, C20.1, C24.1, C29.1, C32.1, C34.1, C37.1, C39.1, C42.1, C44.1, C48.1, C50.1, C51.1, IC1.4 (VEE), IC2.5 (VEE), IC3.5 (VEE), IC4.5 (VEE), IC5.4 (VEE), IC6.5 (VEE), IC7.5 (VEE), IC8.5 (VEE), IC9.5 (VEE), IC10.5 (VEE), IC11.4 (VEE), IC12.4 (VEE), J1.3, U$1.21 (VSS), U$2.21 (VSS), U$3.4 (V-), U$4.4 (V-), U$5.4 (V-), U$6.4 (V-)

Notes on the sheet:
XFADER_ASSIGN v0.1
Designed by Shunichi Yamamoto
05/21/2014
Released under Creative Commons Attribution-Share Alike 4.0 Unported

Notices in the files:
eagle/LineIn.brd:
CC-BY SA 4.0
parts and their libraries:
SparkFun: Licensing: CC v3.0 Share-Alike You are welcome to use this library for commercial purposes.
